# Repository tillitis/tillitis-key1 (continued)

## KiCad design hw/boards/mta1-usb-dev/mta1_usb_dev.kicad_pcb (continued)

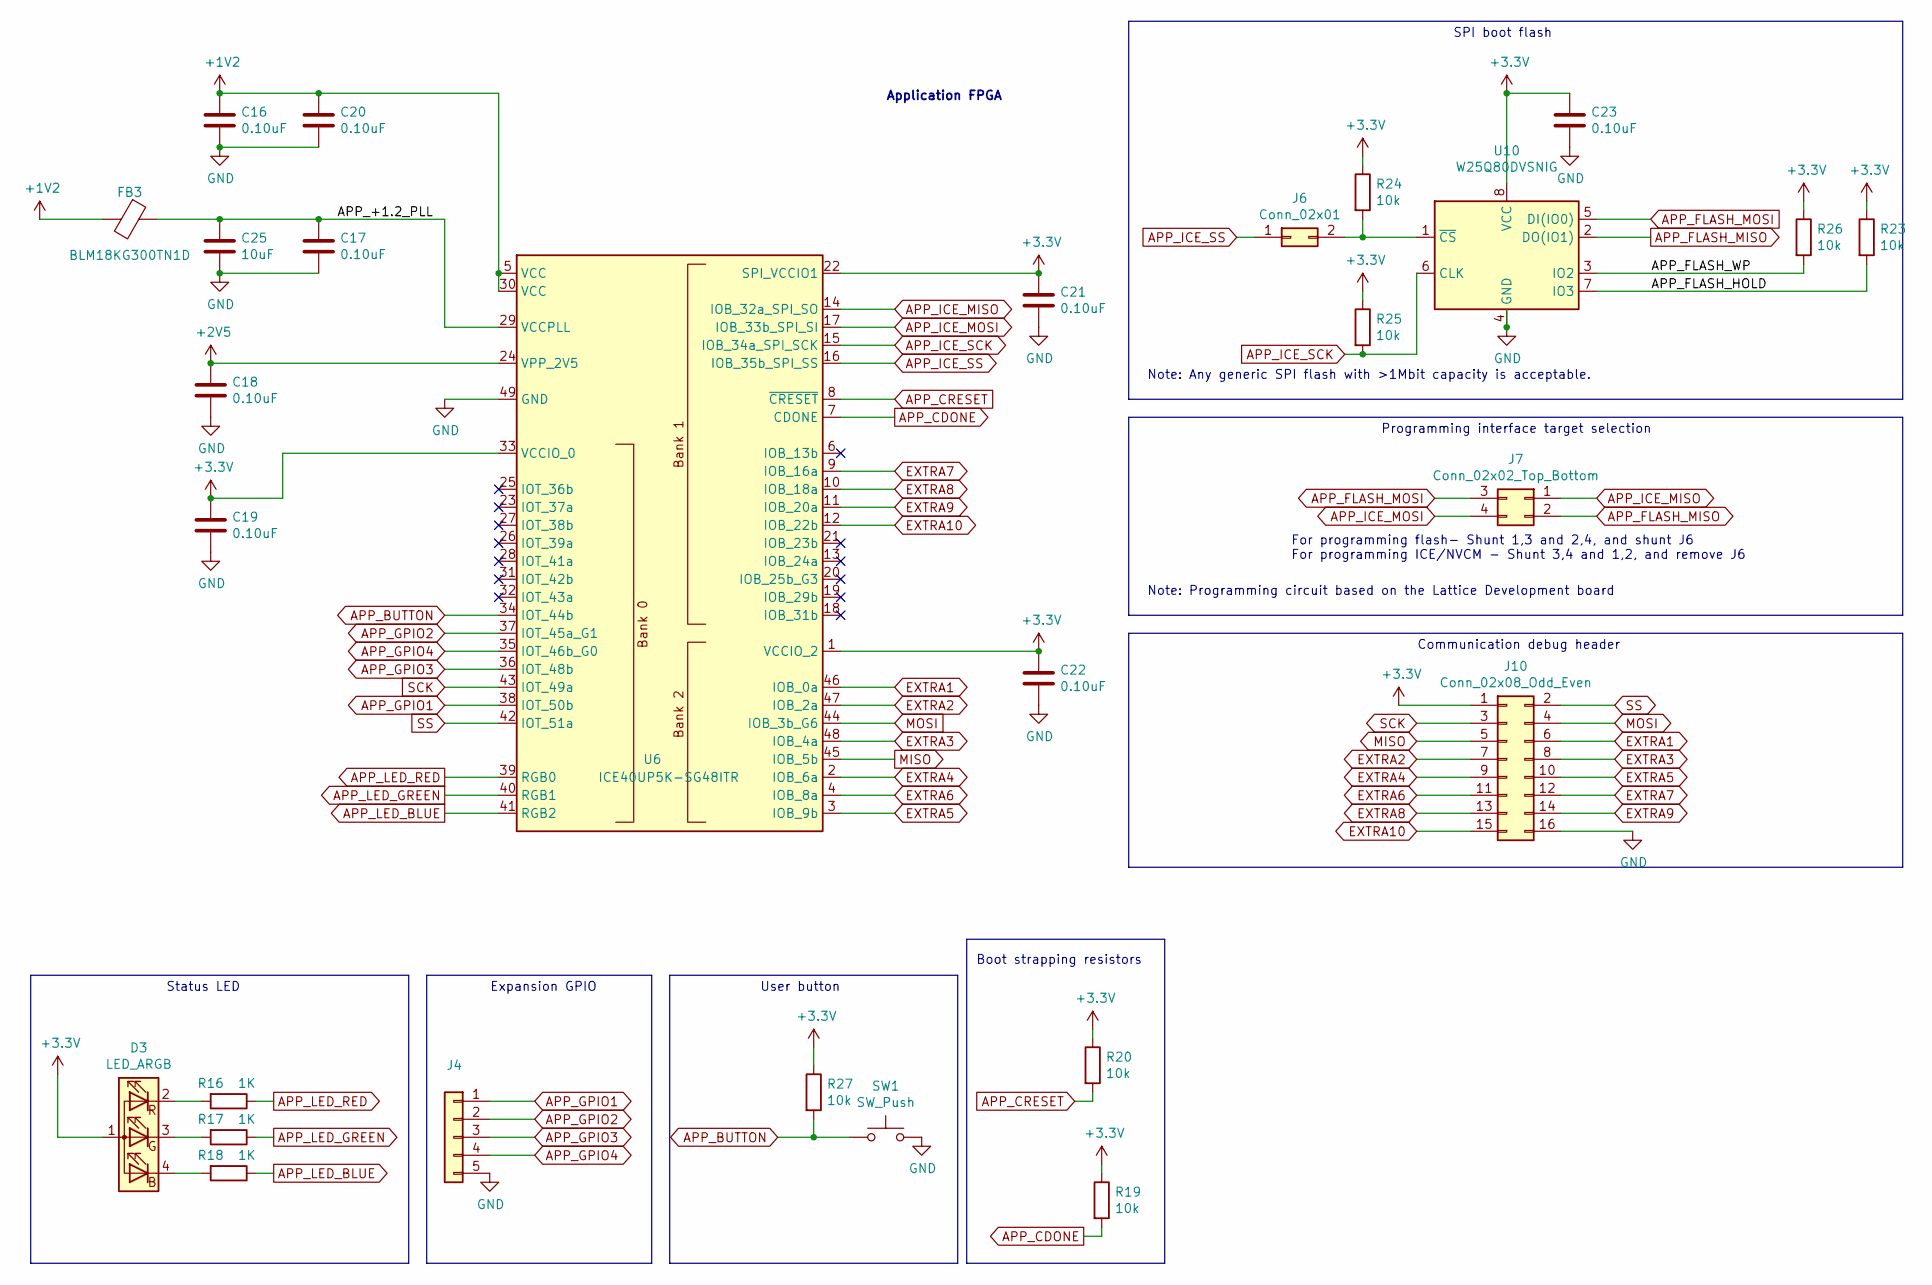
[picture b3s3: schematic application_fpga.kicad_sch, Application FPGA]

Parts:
C16, C17, C18, C19, C20, C21, C22, C23: 0.10uF; CAPC1005X06L
C25: 10uF; CAPC1608X09L
D3: LED_ARGB; 0402rgb-1010
FB3: BLM18KG300TN1D; Ferritbead_0603_1608Metric
J4: PinHeader_1x05_P2.54mm_Vertical
J6: Conn_02x01; PinHeader_1x02_P2.54mm_Vertical
J7: Conn_02x02_Top_Bottom; PinHeader_2x02_P2.54mm_Vertical
J10: Conn_02x08_Odd_Even; PinHeader_2x08_P2.54mm_Vertical
R16, R17, R18: 1K; ERJ2G(0402)_L
R19, R20, R23, R24, R25, R26, R27: 10k; ERJ2G(0402)_L
SW1: SW_Push; SW_Push_SPST_NO_Alps_SKRK
U6: ICE40UP5K-SG48ITR; QFN-48-1EP_7x7mm_P0.5mm_EP5.6x5.6mm
U10: W25Q80DVSNIG; SOIC-8_3.9x4.9mm_P1.27mm

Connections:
+1V2: C16.1, C20.1, FB3.2, U6.5 (VCC), U6.30 (VCC); also elsewhere on the board
+2V5: C18.1, U6.24 (VPP_2V5); also elsewhere on the board
+3V3: C19.1, C21.1, C22.1, C23.1, D3.1 (A), J10.1, R19.1, R20.1, R23.1, R24.1, R25.1, R26.1, R27.1, U6.1 (VCCIO_2), U6.22 (SPI_VCCIO1), U6.33 (VCCIO_0), U10.8 (VCC); also elsewhere on the board
/Application FPGA/APP_+1.2_PLL: C17.1, C25.1, FB3.1, U6.29 (VCCPLL)
/Application FPGA/APP_FLASH_HOLD: R23.2, U10.7 (IO3)
/Application FPGA/APP_FLASH_WP: R26.2, U10.3 (IO2)
APP_BUTTON: R27.2, SW1.1, U6.34 (IOT_44b)
APP_CDONE: R19.2, U6.7 (CDONE); also elsewhere on the board
APP_CRESET: R20.2, U6.8 (~CRESET); also elsewhere on the board
APP_FLASH_MISO: J7.2, U10.2 (DO(IO1)); also elsewhere on the board
APP_FLASH_MOSI: J7.3, U10.5 (DI(IO0)); also elsewhere on the board
APP_GPIO1: J4.1, U6.38 (IOT_50b)
APP_GPIO2: J4.2, U6.37 (IOT_45a_G1)
APP_GPIO3: J4.3, U6.36 (IOT_48b)
APP_GPIO4: J4.4, U6.35 (IOT_46b_G0)
APP_ICE_MISO: J7.1, U6.14 (IOB_32a_SPI_SO)
APP_ICE_MOSI: J7.4, U6.17 (IOB_33b_SPI_SI)
APP_ICE_SCK: R25.2, U6.15 (IOB_34a_SPI_SCK), U10.6 (CLK); also elsewhere on the board
APP_ICE_SS: J6.1, U6.16 (IOB_35b_SPI_SS); also elsewhere on the board
APP_LED_BLUE: R18.1, U6.41 (RGB2)
APP_LED_GREEN: R17.1, U6.40 (RGB1)
APP_LED_RED: R16.1, U6.39 (RGB0)
EXTRA1: J10.6, U6.46 (IOB_0a); also elsewhere on the board
EXTRA2: J10.7, U6.47 (IOB_2a); also elsewhere on the board
EXTRA3: J10.8, U6.48 (IOB_4a); also elsewhere on the board
EXTRA4: J10.9, U6.2 (IOB_6a); also elsewhere on the board
EXTRA5: J10.10, U6.3 (IOB_9b); also elsewhere on the board
EXTRA6: J10.11, U6.4 (IOB_8a); also elsewhere on the board
EXTRA7: J10.12, U6.9 (IOB_16a); also elsewhere on the board
EXTRA8: J10.13, U6.10 (IOB_18a); also elsewhere on the board
EXTRA9: J10.14, U6.11 (IOB_20a); also elsewhere on the board
EXTRA10: J10.15, U6.12 (IOB_22b); also elsewhere on the board
GND: C16.2, C17.2, C18.2, C19.2, C20.2, C21.2, C22.2, C23.2, C25.2, J4.5, J10.16, SW1.2, U6.49 (GND), U10.4 (GND); also elsewhere on the board
MISO: J10.5, U6.45 (IOB_5b); also elsewhere on the board
MOSI: J10.4, U6.44 (IOB_3b_G6); also elsewhere on the board
unnamed: D3.2 (RK), R16.2
unnamed: D3.3 (GK), R17.2
unnamed: D3.4 (BK), R18.2
unnamed: J6.2, R24.2, U10.1 (~CS)
SCK: J10.3, U6.43 (IOT_49a); also elsewhere on the board
SS: J10.2, U6.42 (IOT_51a); also elsewhere on the board

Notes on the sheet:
Application FPGA
Status LED
Expansion GPIO
Programming interface target selection
SPI boot flash
User button
For programming flash- Shunt 1,3 and 2,4, and shunt J6 For programming ICE/NVCM - Shunt 3,4 and 1,2, and remove J6
Note: Any generic SPI flash with >1Mbit capacity is acceptable.
Communication debug header
Note: Programming circuit based on the Lattice Development board
Boot strapping resistors

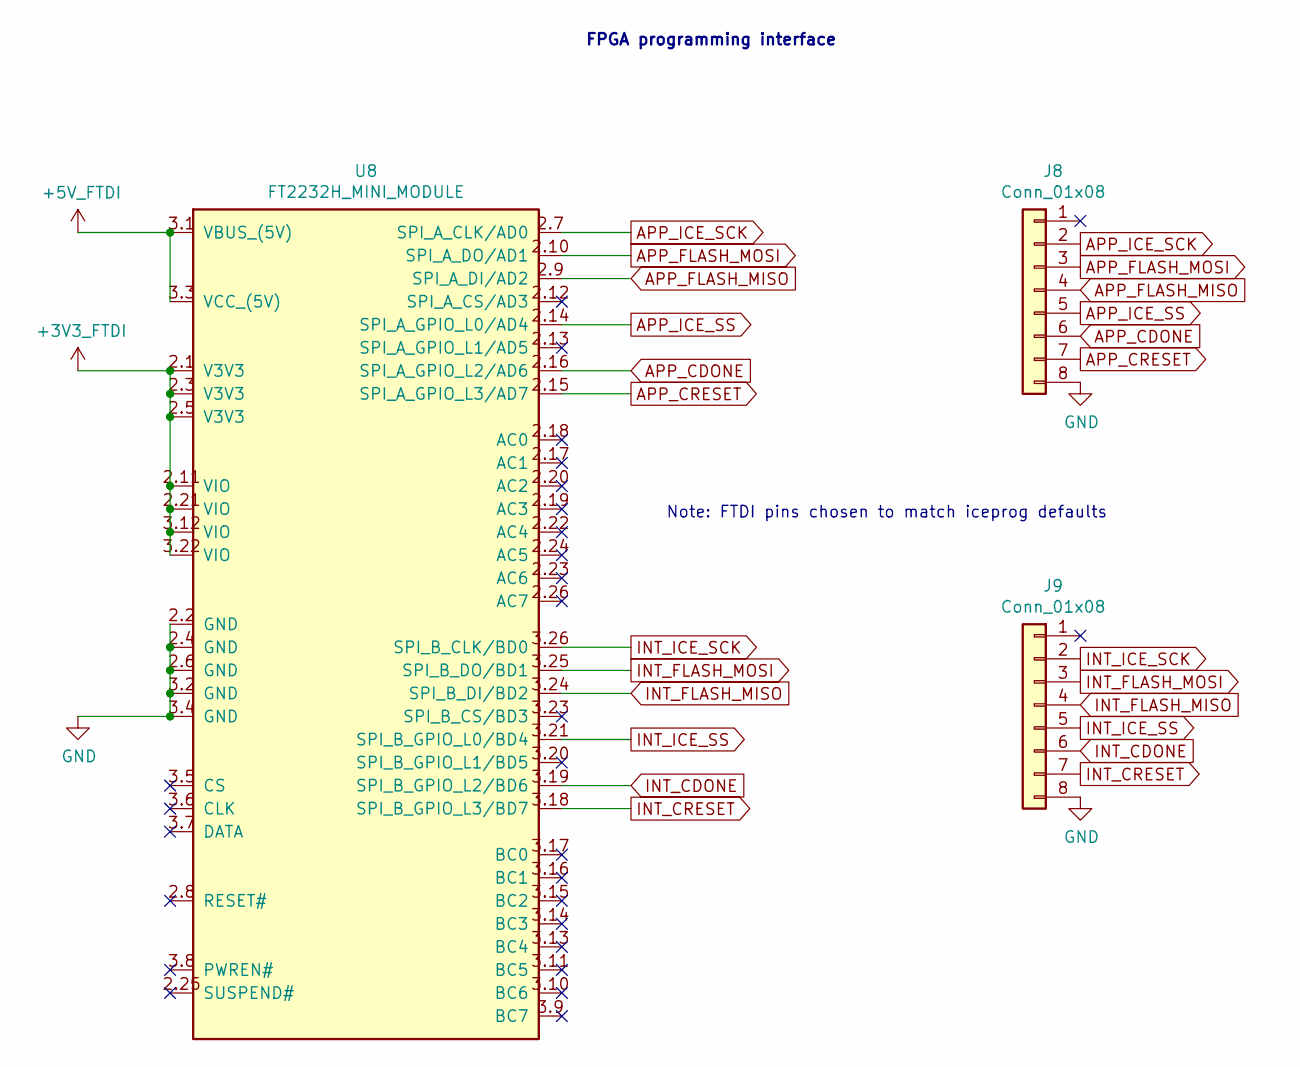
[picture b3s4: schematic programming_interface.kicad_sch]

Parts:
J8, J9: Conn_01x08; PinHeader_1x08_P2.54mm_Vertical
U8: FT2232H_MINI_MODULE

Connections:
+3V3_FTDI: U8.2.1 (V3V3), U8.2.3 (V3V3), U8.2.5 (V3V3), U8.2.11 (VIO), U8.2.21 (VIO), U8.3.12 (VIO), U8.3.22 (VIO)
+5V_FTDI: U8.3.1 (VBUS_(5V)), U8.3.3 (VCC_(5V)); also elsewhere on the board
APP_CDONE: J8.6, U8.2.16 (SPI_A_GPIO_L2/AD6); also elsewhere on the board
APP_CRESET: J8.7, U8.2.15 (SPI_A_GPIO_L3/AD7); also elsewhere on the board
APP_FLASH_MISO: J8.4, U8.2.9 (SPI_A_DI/AD2); also elsewhere on the board
APP_FLASH_MOSI: J8.3, U8.2.10 (SPI_A_DO/AD1); also elsewhere on the board
APP_ICE_SCK: J8.2, U8.2.7 (SPI_A_CLK/AD0); also elsewhere on the board
APP_ICE_SS: J8.5, U8.2.14 (SPI_A_GPIO_L0/AD4); also elsewhere on the board
GND: J8.8, J9.8, U8.2.2 (GND), U8.2.4 (GND), U8.2.6 (GND), U8.3.2 (GND), U8.3.4 (GND); also elsewhere on the board
INT_CDONE: J9.6, U8.3.19 (SPI_B_GPIO_L2/BD6); also elsewhere on the board
INT_CRESET: J9.7, U8.3.18 (SPI_B_GPIO_L3/BD7); also elsewhere on the board
INT_FLASH_MISO: J9.4, U8.3.24 (SPI_B_DI/BD2); also elsewhere on the board
INT_FLASH_MOSI: J9.3, U8.3.25 (SPI_B_DO/BD1); also elsewhere on the board
INT_ICE_SCK: J9.2, U8.3.26 (SPI_B_CLK/BD0); also elsewhere on the board
INT_ICE_SS: J9.5, U8.3.21 (SPI_B_GPIO_L0/BD4); also elsewhere on the board

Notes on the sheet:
Note: FTDI pins chosen to match iceprog defaults
FPGA programming interface

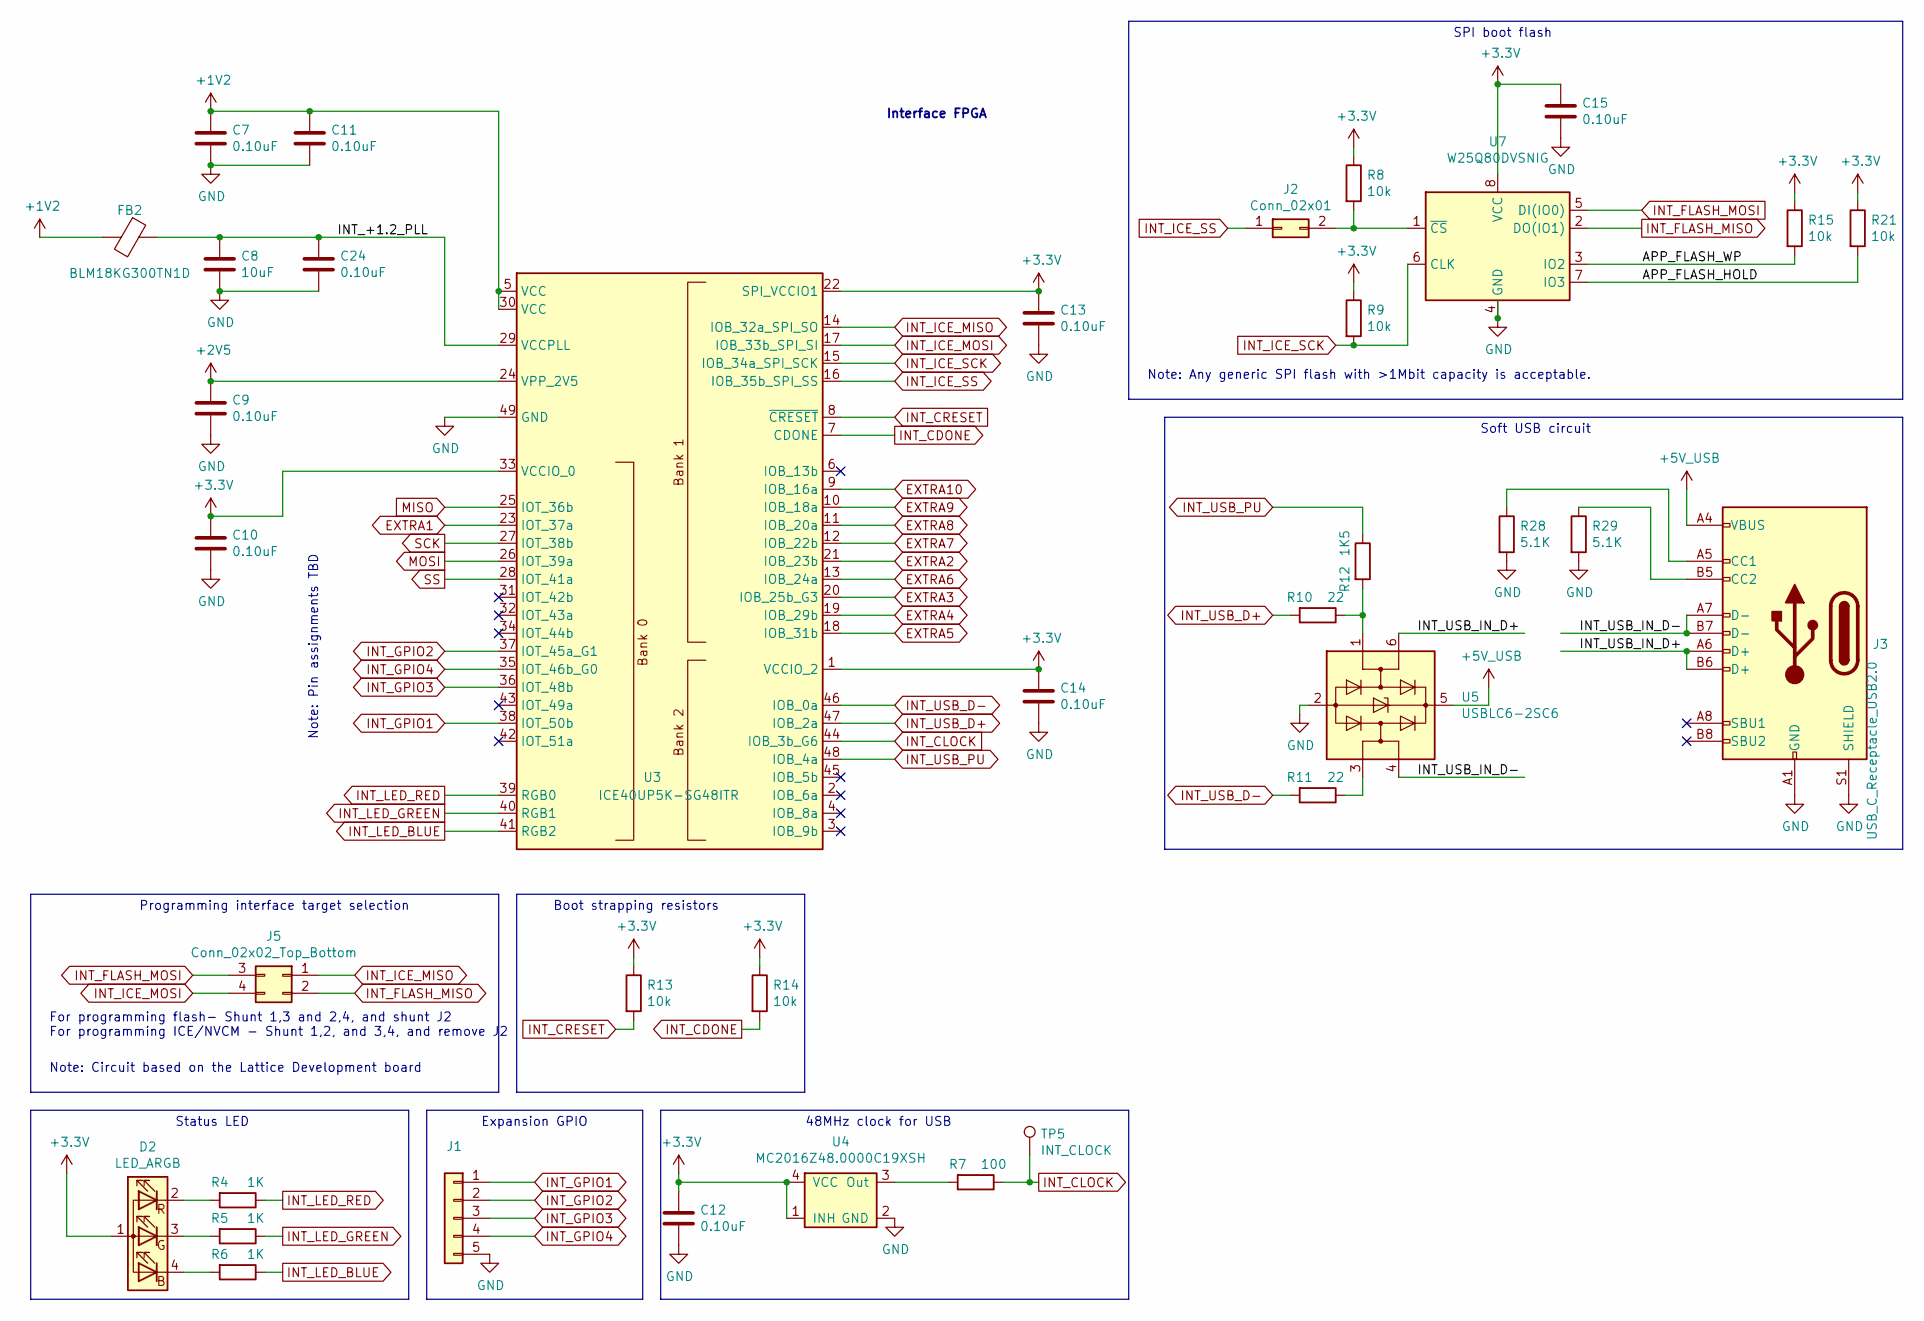
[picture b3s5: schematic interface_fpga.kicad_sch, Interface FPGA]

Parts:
C7, C9, C10, C11, C12, C13, C14, C15, C24: 0.10uF; CAPC1005X06L
C8: 10uF; CAPC1608X09L
D2: LED_ARGB; 0402rgb-1010
FB2: BLM18KG300TN1D; Ferritbead_0603_1608Metric
J1: PinHeader_1x05_P2.54mm_Vertical
J2: Conn_02x01; PinHeader_1x02_P2.54mm_Vertical
J3: USB_C_Receptacle_USB2.0; USB_C_Receptacle_HRO_TYPE-C-31-M-12
J5: Conn_02x02_Top_Bottom; PinHeader_2x02_P2.54mm_Vertical
R4, R5, R6: 1K; ERJ2G(0402)_L
R7: 100; ERJ2G(0402)_L
R8, R9, R13, R14, R15, R21: 10k; ERJ2G(0402)_L
R10, R11: 22; ERJ2G(0402)_L
R12: 1K5; ERJ2G(0402)_L
R28, R29: 5.1K; ERJ2G(0402)_L
TP5: INT_CLOCK; TestPoint_Pad_D1.0mm
U3: ICE40UP5K-SG48ITR; QFN-48-1EP_7x7mm_P0.5mm_EP5.6x5.6mm
U4: MC2016Z48.0000C19XSH; MC2016Z
U5: USBLC6-2SC6; SOT-23-6
U7: W25Q80DVSNIG; SOIC-8_3.9x4.9mm_P1.27mm

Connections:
+1V2: C7.1, C11.1, FB2.2, U3.5 (VCC), U3.30 (VCC); also elsewhere on the board
+2V5: C9.1, U3.24 (VPP_2V5); also elsewhere on the board
+3V3: C10.1, C12.1, C13.1, C14.1, C15.1, D2.1 (A), R8.1, R9.1, R13.1, R14.1, R15.1, R21.1, U3.1 (VCCIO_2), U3.22 (SPI_VCCIO1), U3.33 (VCCIO_0), U4.1 (INH), U4.4 (VCC), U7.8 (VCC); also elsewhere on the board
+5V_USB: J3.A4 (VBUS), J3.A9 (VBUS), J3.B4 (VBUS), J3.B9 (VBUS), U5.5 (VBUS); also elsewhere on the board
/Interface FPGA/APP_FLASH_HOLD: R21.2, U7.7 (IO3)
/Interface FPGA/APP_FLASH_WP: R15.2, U7.3 (IO2)
/Interface FPGA/INT_+1.2_PLL: C8.1, C24.1, FB2.1, U3.29 (VCCPLL)
/Interface FPGA/INT_USB_IN_D+: J3.A6 (D+), J3.B6 (D+), U5.6 (I/O1)
/Interface FPGA/INT_USB_IN_D-: J3.A7 (D-), J3.B7 (D-), U5.4 (I/O2)
EXTRA1: U3.23 (IOT_37a); also elsewhere on the board
EXTRA2: U3.21 (IOB_23b); also elsewhere on the board
EXTRA3: U3.20 (IOB_25b_G3); also elsewhere on the board
EXTRA4: U3.19 (IOB_29b); also elsewhere on the board
EXTRA5: U3.18 (IOB_31b); also elsewhere on the board
EXTRA6: U3.13 (IOB_24a); also elsewhere on the board
EXTRA7: U3.12 (IOB_22b); also elsewhere on the board
EXTRA8: U3.11 (IOB_20a); also elsewhere on the board
EXTRA9: U3.10 (IOB_18a); also elsewhere on the board
EXTRA10: U3.9 (IOB_16a); also elsewhere on the board
GND: C7.2, C8.2, C9.2, C10.2, C11.2, C12.2, C13.2, C14.2, C15.2, C24.2, J1.5, J3.A1 (GND), J3.A12 (GND), J3.B1 (GND), J3.B12 (GND), J3.S1 (SHIELD), R28.2, R29.2, U3.49 (GND), U4.2 (GND), U5.2 (GND), U7.4 (GND); also elsewhere on the board
INT_CDONE: R14.2, U3.7 (CDONE); also elsewhere on the board
INT_CLOCK: R7.1, TP5.1, U3.44 (IOB_3b_G6)
INT_CRESET: R13.2, U3.8 (~CRESET); also elsewhere on the board
INT_FLASH_MISO: J5.2, U7.2 (DO(IO1)); also elsewhere on the board
INT_FLASH_MOSI: J5.3, U7.5 (DI(IO0)); also elsewhere on the board
INT_GPIO1: J1.1, U3.38 (IOT_50b)
INT_GPIO2: J1.2, U3.37 (IOT_45a_G1)
INT_GPIO3: J1.3, U3.36 (IOT_48b)
INT_GPIO4: J1.4, U3.35 (IOT_46b_G0)
INT_ICE_MISO: J5.1, U3.14 (IOB_32a_SPI_SO)
INT_ICE_MOSI: J5.4, U3.17 (IOB_33b_SPI_SI)
INT_ICE_SCK: R9.2, U3.15 (IOB_34a_SPI_SCK), U7.6 (CLK); also elsewhere on the board
INT_ICE_SS: J2.1, U3.16 (IOB_35b_SPI_SS); also elsewhere on the board
INT_LED_BLUE: R6.1, U3.41 (RGB2)
INT_LED_GREEN: R5.1, U3.40 (RGB1)
INT_LED_RED: R4.1, U3.39 (RGB0)
INT_USB_D+: R10.2, U3.47 (IOB_2a)
INT_USB_D-: R11.2, U3.46 (IOB_0a)
INT_USB_PU: R12.1, U3.48 (IOB_4a)
MISO: U3.25 (IOT_36b); also elsewhere on the board
MOSI: U3.26 (IOT_39a); also elsewhere on the board
unnamed: D2.2 (RK), R4.2
unnamed: D2.3 (GK), R5.2
unnamed: D2.4 (BK), R6.2
unnamed: J2.2, R8.2, U7.1 (~CS)
unnamed: J3.A5 (CC1), R28.1
unnamed: J3.B5 (CC2), R29.1
unnamed: R7.2, U4.3 (Out)
unnamed: R10.1, R12.2, U5.1 (I/O1)
unnamed: R11.1, U5.3 (I/O2)
SCK: U3.27 (IOT_38b); also elsewhere on the board
SS: U3.28 (IOT_41a); also elsewhere on the board

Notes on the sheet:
Expansion GPIO
48MHz clock for USB
Note: Any generic SPI flash with >1Mbit capacity is acceptable.
Boot strapping resistors
Soft USB circuit
Note: Circuit based on the Lattice Development board
Status LED
Programming interface target selection
Interface FPGA
Note: Pin assignments TBD
For programming flash- Shunt 1,3 and 2,4, and shunt J2 For programming ICE/NVCM - Shunt 1,2, and 3,4, and remove J2
SPI boot flash

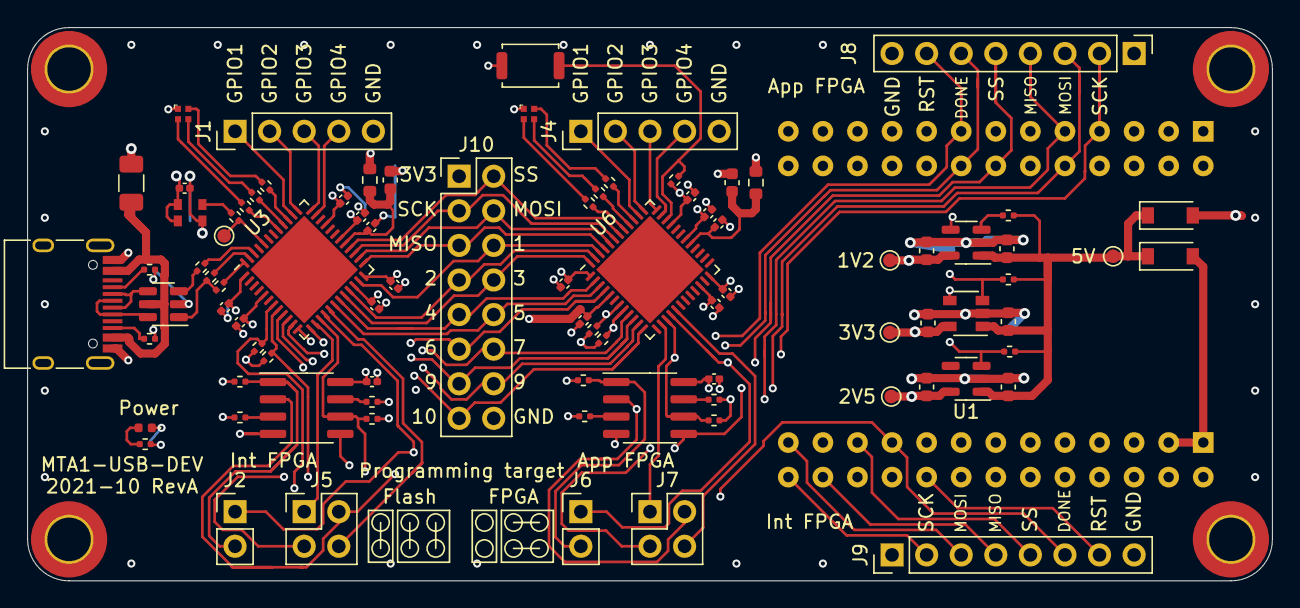
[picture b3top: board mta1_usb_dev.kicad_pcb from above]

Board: 4 copper layers, 91.4 x 40.6 mm, 92 parts (0 on the bottom side), 83 nets.

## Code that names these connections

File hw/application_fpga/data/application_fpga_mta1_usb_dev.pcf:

#=======================================================================
#
# application_fpga_mta1_usb_dev.pcf
# ---------------------------------
# Pin constraints file for the Application FPGA design used on the
# Tillitis MTA1_USB_DEV board.
#
#
# Copyright (C) 2022 - Tillitis AB
# SPDX-License-Identifier: BSD-2-Clause
#
#=======================================================================

# UART.
set_io interface_rx 15
set_io interface_tx 16
#set_io interface_cts 27
#set_io interface_rts 28


# Touch sense, mapped to a switch.
set_io touch_event 23


# GPIOs.
set_io app_gpio1 26
set_io app_gpio2 27
set_io app_gpio3 31
set_io app_gpio4 32


# LEDs
set_io led_r 41
set_io led_g 40
set_io led_b 39

#=======================================================================
# EOF application_fpga_usb_dev.pcf
#=======================================================================

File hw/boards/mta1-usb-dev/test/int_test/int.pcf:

# Host Communication
set_io HOST_SS      28
set_io HOST_SCK     27
set_io HOST_MOSI    26
set_io HOST_MISO    25

set_io HOST_EXTRA1  23
set_io HOST_EXTRA2  21
set_io HOST_EXTRA3  20
set_io HOST_EXTRA4  19
set_io HOST_EXTRA5  18
set_io HOST_EXTRA6  13
set_io HOST_EXTRA7  12
set_io HOST_EXTRA8  11
set_io HOST_EXTRA9  10
set_io HOST_EXTRA10 9

# USB
#set_io INT_USB_D-   46
#set_io INT_USB_D+   47
#set_io INT_USB_PU   48

set_io INT_CLOCK    44

# Expansion
set_io INT_GPIO1    38
set_io INT_GPIO2    37
set_io INT_GPIO3    36
set_io INT_GPIO4    35

## User IO
set_io RGB0         39
set_io RGB1         40
set_io RGB2         41

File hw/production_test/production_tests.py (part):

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    'cdne': 15,
    'rts': 16,
    'cts': 17,
    'gpio1': 18,
    'gpio2': 19,
    'gpio3': 20,
    'gpio4': 21,
}


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

def test_extra_io() -> bool:
    """Test the TK-1 RTS, CTS, and GPIO1-4 lines"""

    flasher = IceFlasher()
    for pin in TP1_PINS.values():
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
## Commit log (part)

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2025-05-15 Update binary hashes for bitstream & firmware
2025-05-16 fw: Add debug print when reading partition table fails
2025-05-16 tool: Add docs to partition_table
2025-05-16 Reset USB controller endpoints when starting
    When starting, reset the USB controller to only enable the USB CDC
    endpoint and the internal command channel. If the app resets firmware,
    but had differend endpoints enabled, we want to go back to a known
    state.
2025-05-19 ch552: Make CTS pins configurable
2025-05-19 fpga: Update seed to reach 24 MHz
2025-05-19 fpga: Set default app to defaultapp.bin
2025-05-20 Update binary hashes for bitstream
2025-05-20 doc: Link to firmware docs from TKey hardware design
2025-05-20 Remove superfluous file __init__.py
2025-05-22 doc: Correct the GPL file
    Import file
    https://www.gnu.org/licenses/old-licenses/gpl-2.0.txt
    verbatim since it clearly says in the license that we are now allowed
    to change it. I think it might have been a cut and paste from
    https://www.gnu.org/licenses/old-licenses/gpl-2.0.html
    before?
2025-05-22 doc: Complete copyright and licenses
    - Point out licensing terms in docs.
    - Add missing SPDX tags
    - Update the SPDX checker to check all the files we want to check.
    - Include spdx-ensure in CI.
2025-05-22 build: Do not use sudo when running tillitis-iceprog
2025-05-23 doc: Mention the tkeyimage tool in firmware README
2025-05-23 doc: Add description on how to build and flash USB controller firmware
2025-05-28 doc: Describe how to test alpha release in release notes
    Adds information and link on how to test alpha release.
2025-06-24 Add make targets for building CH552 firmware with podman
2025-06-27 Update USB product descriptor for Castor
2025-06-27 Fix allowed_app_digest formatting
    Fix formating of BLAKE2s digest of app allowed to start from
    flash slot 0.
2025-07-17 toolchain: Add Go package
    - Add Go 1.23.
    - Set up PATH for container to include the Go binaries.
2025-08-28 tool: Change b2s to output exact variable used
    - Use correct name.
    - Don't declare it as static.
    - Lose the toolchain
    - Use only basename of path in the b2s comment
2025-08-29 build: Introduce DEFAULT_APP with automatic builds
    Introduce the Makefile variable DEFAULT_APP which should be the path
    to the device app binary to include in the obliagory slot 0.
    Build automatically: the default app, the new digest file
    mgmt_app_digest.h for the firmware which contains the digest of
    DEFAULT_APP, the default partition table, and all the tools necessary
    to generate this.
2025-08-29 build: Remove all built qemu artefacts when cleaning
2025-09-01 build: Create and use a complete filesystem image
    - Create a flash image in flash_image.bin, useful for both a real TKey
    and QEMU.
    - Use flash_image.bin directly in prog_flash for a real TKey, which
    also flashes the bitstream.
    - Remove building of tools/default_partition.bin.
    - Update documentation about the tool use.
2025-09-02 build: Run static code analysis after fw build
    Since we now generate at least one source code file we need to run the
    static code analysis after the build.
2025-10-02 tool: Support app1 in tkeyimage
    - Add support for an app in slot 1.
    - Sign the digest of the app. Store both digest and signature in
    partition table.
2025-10-02 build: firmware.elf depend on digest of flash app 0
    Firmware depends on the expected content of the flash. Not the actual
    content of the flash.
2025-10-25 build multiarch (amd64,arm64) docker image
2025-10-27 fpga: Update next-pnr seed to reach 24 MHz
2025-10-28 uart: Make CTS active low, as per the standard
2025-10-30 Change license to BSD-2-Clause
    This was announced on the Tillitis Blog the 2nd of October 2024, for
    more info visit https://tillitis.se
2025-11-10 testapp: Print out the CDI
    For test purposes, print the normally secret CDI
2025-11-13 ch552: add zero length packet handling
    Terminate all 64-byte frames with a zero-length packet. Handle incoming
    zero-byte frames by ignoring them. This fix addresses issues related to
    transfers of an exact length of 64 bytes (or multiples thereof) on all
    platforms. For simplicity, all 64-byte frames are terminated, regardless
    of whether they are the last or not.
2025-12-03 tool: Mention preloaded app and its signature in tkeyimage README
2025-12-03 build: Import TP-1 programming board on both run and flash targets
    - Import TP-1 programming board on both run and flash.
    - Import only TP-1, not any other USB devices.
2025-12-05 temporary change to test timer bug in qemu
2025-12-05 Move resetinfo cleaning
2025-12-12 fw: Add app pubkey to partition table
    - Pubkey is read-only and stored in the partition table.
    - preload_get_digsig is updated to also fetch the pubkey
2025-12-15 tool: Add -app1pub flag to tkeyimage
    The -app1pub flag can be used to populate the partition tables pubkey
    field.
2025-12-16 doc: Update fw/README.md
    - Clarify TKey Unlocked in firmware definition, avoiding to introduce
    new concept "usual consumer TKey"
    - Nits and typos
    - Fix table waitcommand
    - Explain USS from user perspective
    - Add link to top readme
2025-12-18 ch552-debugging
2025-12-19 Modifications that seems to lower the chance of corrupted data
    - Slow down EP0 by NAK
    - Remove some memcpy, making data accessing faster
    - Tested with poll EP0 at 2ms
    - Tested with write to fw at 51 ms
2025-12-22 doc: More threat model revisions
    - Simplify language.
    - Mark things to investigate and/or implement.
    - Add note about the security boundary.
    - Add note about the UDS in provisioning.
    - Remove remnants of threats in wrong places.
    - Clarify mitigations for FW_RAM.
2026-01-08 flip correct tx/rx pins
2026-01-12 ch522: use memcpy_local to avoid register corruption
    Fixes possible data corruption if EP0 is aggressively queried.
    The SDCC mcs51 memcpy() uses fixed registers and is not reentrant, so it
    can be corrupted if interrupted by an ISR. This implementation is
    reentrant, given that source and destination buffers are not accessed
    concurrently. Use this instead of memcpy() if it could be interrupted.
2026-01-12 ch552: change uint32_t to uint8_t for circular_copy
    Use uint8_t for all lengths in circular_copy(), increment_pointer() and
    decrement_pointer(). Limits the maximum length to 255, but since the
    longest buffer is 140 bytes it is enough. The CH552 is an 8-bit mcu
    uint32_t is expensice. This lowers the app binary with with approx 900
    bytes.
2026-01-13 doc: Update threat model
    - Clearly express that it's the *firmware* that can't leak the USS
    passphrase.
    - Note that device app's don't have access to the USS digest.
2026-01-14 ch552: use 256 bytes UART rx buffer, and optimize for it
    - A 256 byte buffers wraps naturally with uint8_t variables, optimize in
    UART ISR
    - Remove size input for increment_pointer, only allow 256 byte buffers
    - Adapt size input for circular_copy, to accommodate for 256 byte buffer
2026-01-14 ch552: remove size for circular_copy
2026-01-14 ch552: inline subroutines
    Inline as many subroutines as possible in order to optimize on time
2026-01-14 ch552: fix warning 283: function declarator with no prototype
2026-01-15 temporary: invert cts to old behaviour for testing
2026-01-16 doc: Correct links in readme for tkeyimage
2026-01-16 build/fw: Turn on clang static analyzer checks
2026-01-23 fw: Calculate different CDI depending on how an app was loaded
    A `domain` byte is added to the data that is hashed to produce the CDI.
    The value of the domain byte mirrors the value that is present in
    `resetinfo->type`.
    This makes it harder for an app loaded from one source to impersonate an
    app loaded from another source. An app loaded from the client will not
    get the same CDI as an app loaded from flash.
2026-01-26 doc: Amend threat model more
    - Update TL;DR.
    - List threats of impersonation of CDI.
    - Remove unnecessary detail and instead point to more documentation.
    - Add user presence were needed.
2026-01-27 doc: threat model: Fix broken internal link
2026-01-28 fw: Rename SYS_PRELOAD_GET_DIGSIG to SYS_PRELOAD_GET_METADATA
2026-01-29 fw: Add syscall to write pubkey to flash
    Any existing pubkey is overwritten
2026-01-30 doc: fw README: PRELOAD_GET_DIGSIG -> PRELOAD_GET_METADATA
2026-01-30 build: Update fw and bitstream digests
    build: Update fw and bitstream digests
2026-02-02 fw: Check that syscall user data is in app RAM
    - Adds the function in_app_ram() which can be used to check if data is
    located in app RAM.
    - Syscalls: Use in_app_ram() to check that data received through
    pointers is located in app RAM.
2026-02-03 build: tkeyimage Use new signature types from signify packages
2026-02-09 fw: Add domain byte to CDI computation
    A `domain` byte is added to the data that is hashed to produce the CDI.
2026-02-09 fw: Use different CDI-domain if USS is used
2026-02-09 doc: Threat model: More about impersonation
2026-02-13 fw: Expand domain byte to string
    Use the domain byte as a bitstring index into a string array with a
    set of fixed size strings, indicating which combination we will use
    for the CDI computation:
    Domain strings are indexed by toggling bits. Set means on. Bit 0
    is USS, bit 1 is chained.
    Bitstring | Value | Comment
2026-02-17 fw: Reclaim unused ROM in start.S
    Save 64 byte by moving init from 0x100 to 0xc0
2026-02-18 fw: Remove unnecessary start.S code
    Removing:
    - Setting the zero register to zero. It will generate a nop.
    - Loop clearing .bss. Bss is in FW_RAM.
2026-02-20 doc: Revise firmware README
    Describe the use of keyed BLAKE2s and what is used as the key.
2026-02-20 doc: Update threat model for new generation: Castor
    - Add a clear TL;DR.
    - List many more assets.
    - List major threats and mitigations to them under every asset
    heading.
    - Remove old releases. If you want to look what was mitigated in an
    earlier release, just look at the same document in that release.
2026-03-30 doc: Clarify threat model
    - Make it clearer that we belive that if someone runs our boot
    verifier we guarantee that the computed *secret* will be the same
    only when a vendor's key material is also used.
    - Remove the physical access requirement from Denial of Service. We
    don't consider it a real Denial of Service if someone manages to, for
    instance, send a command that makes the firmware stop the TKey, but
2026-06-25 Update hash for application_fpga.bin
    Include changes for package uwg30
2026-06-25 ch552: Deactivate CTS early
    Deactivating CTS early to increase the chance that it has the correct
    state when the other end samples it the first time.
2026-06-25 fw/ch552: Enable USB endpoints after a SET_ENDPOINTS command is received
    Instead of always enabling USB endpoints at boot we let the firmware or
    app that intend to receive data decide when to enable them.
    This allows a client to know when to send data after a reset.
